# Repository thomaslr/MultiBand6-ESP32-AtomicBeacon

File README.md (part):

# MultiBand6-ESP32-AtomicBeacon: Hardware Atomic Clock Simulator

An open-hardware, low-power near-field radio transmitter built on the **ESP32-C3-Mini** with custom PCB designs, resonant magnetic antenna, 3D enclosure, and embedded web UI. Simulates authentic LF radio time signal broadcasts (**BPC, WWVB, MSF, DCF77, JJY40, JJY60**) to synchronize radio-controlled ("atomic") wristwatches and clocks over a localized range (~0.3 m to 1.0 m).

### 🏠 Real-World Setup & Confirmed Working
> **Built and actively in daily operation in Singapore!**  
> Since Singapore receives no LF signals from any of the official time towers, this device was built to solve that problem. It runs quietly every night on a bedroom nightstand, placed approximately **30 cm from a watch box**, successfully synchronizing a multi-watch collection every single night.
> 
> *(Compatible with all radio-controlled timepieces including **Casio G-Shock / Oceanus / Wave Ceptor / Lineage**, **Citizen Eco-Drive**, **Seiko**, **Timex**, **Junghans**, and standalone atomic desk clocks).*

| Assembled Hardware & Antenna | Bedroom Watch Box Deployment | 3 MultiBand 6 Watches Synced |
| :---: | :---: | :---: |
|  |  |  |
| *Custom 2-layer PCB with ESP32-C3 SuperMini & magnetic inductor antenna.* | *Operational placement ~30 cm from the watch box on the nightstand.* | *Simultaneous sync proof: Casio Wave Ceptor (`GET 1:02`), Lineage Chronograph, and Lineage Ana-Digi.* |

> [!IMPORTANT]
> **Wi-Fi & Network Time Requirement:**  
> The beacon does not contain a battery-backed hardware RTC chip. On boot and prior to each broadcast, it connects to your home 2.4 GHz Wi-Fi to fetch sub-second reference time from public NTP atomic clock servers (`pool.ntp.org`).  
> 
> **Placement Tip:** Place the beacon in a location with steady Wi-Fi reception (e.g. bedside or near your watch box where home Wi-Fi reaches). If placed in a Wi-Fi-dark dead zone on cold boot, the device cannot obtain the initial atomic epoch, and watch broadcasts/sync buttons will remain locked until time synchronization completes.

> [!TIP]
> 🚀 **Just want to get your watch syncing tonight?**  
> Check out the **[5-Minute Quick Start Guide](QUICKSTART.md)** for 1-click in-browser web flashing — zero software installation or coding required! For watch brand setup notes, see the **[Watch Compatibility Guide](CASIO_GUIDE.md)**.

---

## 1. Bill of Materials (BOM) & Components

| Component | Value / Specification | Role in Circuit | Rationale / Notes |
| :--- | :--- | :--- | :--- |
| **Microcontroller** | **ESP32-C3-Mini** | Core Controller & Carrier Generator | Single-core 32-bit RISC-V (160 MHz), hardware LEDC PWM with fractional clock divider, RTC timer, Wi-Fi 4, BLE 5. |
| **NPN Transistor** | **C1815 (2SC1815)** | Power Switch / RF Driver (Option A) | Small-signal NPN transistor (TO-92 package, E-C-B pinout) switching the LC tank at 5V for extended 1.0 m+ range. *(Note: You could also use a 2p2222 / 2N2222, but that transistor's different E-B-C pinout must be respected!)* |
| **Base Resistor ($R_{base}$)** | **$1\text{ k}\Omega$ (1/4 W)** | Transistor Base Drive (Option A) | Connects between GPIO 1 and C1815 Base (Pin 3). Limits base drive current to a safe $\sim 2.6\text{ mA}$ for saturation switching. |
| **Inductor ($L$)** | **16×18 3.5mH I-Type Inductor** | Magnetic Antenna ($H$-field radiator) | The reference hardware build specifically uses a **16×18 mm 3.5 mH I-type** (radial drum/bobbin core) power inductor. Its open magnetic circuit allows magnetic dipole flux lines to radiate into the room with low DC resistance. |
| **Tuning Capacitor ($C$)** | **1.5 nF (1500 pF / code `152`)** | Parallel LC Tank Resonator | Metallized Film (CBB / Polypropylene / Polyester) or C0G/NP0 ceramic. Rated $\ge 50\text{V}$. |
| **Damping Resistor ($R_{damp}$)** | **$220\,\Omega$ (1/4 W)** | Bandwidth Broadening & Safety Current Limiter | Lowers tank $Q$ to $\sim 6.5$, broadening bandwidth to $\sim 10\text{ kHz}$. Limits peak current to $\approx 23\text{ mA}$ in transistor booster or $\approx 15\text{ mA}$ in direct GPIO drive. |
| **DC Blocking Cap ($C_{block}$)** | **$1\,\mu\text{F}$ (or $100\text{ nF}$)** | DC Isolation & GPIO Protection (Option B) | Only required if running Option B (Direct GPIO Drive without transistor). Completely blocks DC current so pin cannot burn out if stuck `HIGH`. |

---

## 2. Hardware Circuit Schematics & Pinout

### Default Pin Assignment & ESP32-C3 SuperMini Pinout

The firmware defaults to **GPIO 1** for the antenna carrier output (`#define ANTENNA_PIN 1` in `src/main.cpp`).

| Board Pin | ESP32-C3 Signal | Role | Circuit Connection |
| :--- | :--- | :--- | :--- |
| **GPIO 1** | `IO1` (LEDC Ch 0) | **Default RF Carrier Out** | Connects to base resistor ($1\text{ k}\Omega$) driving booster NPN transistor, or direct antenna |
| **GPIO 2** | `IO2` | *(Unconnected)* | Strapping pin on ESP32-C3; reserved to prevent USB flashing and cold-boot issues |
| **GPIO 3** | `IO3` (Active LOW) | **Manual Sync Pushbutton** | Connects to tactile button `SW1` / external header `J3` with 10 kΩ pull-up |
| **GPIO 4** | `IO4` (I2C SDA) | **I2C Expansion (OLED)** | Connects to `J2` Pin 4 with 4.7 kΩ pull-up for 0.96" SSD1306 OLED display |
| **GPIO 5** | `IO5` (I2C SCL) | **I2C Expansion (OLED)** | Connects to `J2` Pin 3 with 4.7 kΩ pull-up for 0.96" SSD1306 OLED display |
| **GPIO 8** | `IO8` (Active LOW) | **Onboard Status LED** | Breathing nightstand pulse during active broadcast; 100% dark in standby |
| **5V / VIN** | `VBUS` (USB 5V) | Primary Power Rail | Supplies the booster circuit & damping resistor |
| **GND** | `GND` | Common Ground Return | Connects to transistor Emitter, capacitor ground, and ground plane |

> [!TIP]
> **Custom PCBs Available:**
> - **SMT Carrier Board (58×36 mm):** Located in [`pcb/smd/`](pcb/smd/) (or symlink [`smd/`](smd/)), uses 100% JLCPCB Basic Components ($0 setup fees) for fast turnkey assembly.
> - **Through-Hole DIY Edition (70×46 mm):** Located in [`pcb/hole-through/`](pcb/hole-through/) (or symlink [`hole-through/`](hole-through/)), 100% hand-solderable with standard through-hole passives, TO-92 transistor, DO-41 diode, and M3 mounting holes. Zero SMD parts required. See [`hole-through/README.md`](hole-through/README.md) for BOM and build guide.

> **Why GPIO 1?**
> * **Boot & Flashing Safety:** On the ESP32-C3, GPIO 2, 8, and 9 are hardware strapping pins. Pulling GPIO 2 low (which occurs when driving an NPN transistor base to ground) prevents entering Download Boot mode over USB and causes boot lockups. **GPIO 1 is a pure GPIO/ADC with zero strapping functions**, allowing reliable cold boots and in-circuit flashing over USB.
> * **LEDC Peripheral:** Native hardware routing to LEDC channel 0 with fractional divider clocking.
> * **Physical Placement:** Located on the accessible edge header directly adjacent to Pin 6 on the **ESP32-C3 SuperMini** (Pin 7).

```
      TOP VIEW (Component Side — looking at chip & buttons)
                       ┌───[ USB-C ]───┐
     [BOOT Button Side]│               │[RST Button Side]
              GPIO 5   │ [ ]       [ ] │   5V          <── Top-Right (next to USB)
              GPIO 6   │ [ ]       [ ] │   GND (G)     <── Next to 5V
              GPIO 7   │ [ ]       [ ] │   3V3 (3.3)   <── Regulated 3.3V
              GPIO 8   │ [ ]       [ ] │   GPIO 4
              GPIO 9   │ [ ]       [ ] │   GPIO 3
             GPIO 10   │ [ ]       [ ] │   GPIO 2
             GPIO 20   │ [ ]       [■] │   GPIO 1      <── [■] ANTENNA OUT (Pin 7)
   (Pin 21)  GPIO 21   │ [ ]       [ ] │   GPIO 0      (Pin 0)
                       └──[ Antenna ]──┘

      BOTTOM VIEW (Underside — looking at PCB silkscreen labels)
                       ┌───[ USB-C ]───┐
                       │               │
     Top-Left (5V) ──► │ [ ]       [ ] │   GPIO 5
              GND (G)  │ [ ]       [ ] │   GPIO 6
            3V3 (3.3)  │ [ ]       [ ] │   GPIO 7
               GPIO 4  │ [ ]       [ ] │   GPIO 8
               GPIO 3  │ [ ]       [ ] │   GPIO 9
               GPIO 2  │ [ ]       [ ] │   GPIO 10
   ANTENNA OUT ──────► │ [■]       [ ] │   GPIO 20
     (Pin 0)   GPIO 0  │ [ ]       [ ] │   GPIO 21     (Pin 21)
                       └───────────────┘
```

---

### Option A: C1815 NPN Transistor Booster Circuit (Recommended for 1.0 m+ Range)

This configuration uses the **C1815 (2SC1815) NPN** transistor powered directly from the **5V USB rail**. It isolates the ESP32 silicon and delivers $3\times$ to $5\times$ more magnetic flux for extended range:

```
                                  +5V (from ESP32 5V / VIN Pin)
                                    │
                                    ├───[ 220 ohm ]─── (R_damp)
                                    │
                                    ├───┬───────────────┬───┐
                                     │   │               │   │
                                     │  [16x18 3.5mH] [ 1.5 nF ]  (Parallel LC Tank)
                                     │  (I-type Ind.) (Capacitor)
                                     │   │               │   │
                                     └───┴───────────────┴───┘
                                                 │
                                                 ▼
                                          [ C ] Collector (Pin 2)
   ESP32-C3 GPIO 1 ──[ 1k ohm ]────────── [ B ] Base (Pin 3)       C1815 NPN Transistor
   (Default PWM Out) (R_base)             [ E ] Emitter (Pin 1)
                                                 │
                                                 ▼
   ESP32-C3 GND ─────────────────────────────────┴─── Common Ground (GND)
```

#### Why This Works Well:
1. **Zero Stress on ESP32:** The GPIO 1 pin only sources a safe $I_B \approx 2.6\text{ mA}$ into the base through the $1\text{ k}\Omega$ base resistor ($V_{GPIO} = 3.3\text{V}$, $V_{BE} \approx 0.7\text{V}$).
2. **5V Swing:** The LC tank swings around the 5V rail rather than 3.3V, pushing significantly more magnetic current through the 3.5 mH inductor.
3. **Uses Your $220\,\Omega$ Resistor:** The $220\,\Omega$ damping resistor limits peak collector current to a cool, safe $\approx 23\text{ mA}$ while maintaining the broad $\sim 10.7\text{ kHz}$ bandwidth so 68.5 kHz BPC resonates smoothly.
4. **Broadcast Range:** Up to **1.0 m – 1.2 m**.

#### C1815 Transistor Pinout & Pinout Connections (TO-92 Package)

The circuit is designed specifically around the **C1815 (2SC1815)** small-signal NPN transistor.

Looking at the **flat printed face** (labeled "C1815") with the leads pointing downwards, the pinout follows the standard Asian / JIS **E-C-B** configuration:

```
          TO-92 Package (Front View)
               ┌───────────┐
               │   C1815   │   <── Flat Printed Face
               │   GR 331  │
               └─┬───┬───┬─┘
                 │   │   │
                 1   2   3
                 E   C   B
```

| Pin # | Lead Name | Circuit Function | Breadboard Connection |
| :---: | :--- | :--- | :--- |
| **Pin 1 (Left)** | **Emitter (E)** | Common Ground Return | Connects directly to **(-) Blue GND Rail** (Row 13) |
| **Pin 2 (Center)** | **Collector (C)** | Switched LC Tank Low Side | Connects to **Row 12** (bottom of 3.5 mH inductor & 1.5 nF cap) |
| **Pin 3 (Right)** | **Base (B)** | RF Carrier PWM Input | Connects to **Row 11** (receives drive from GPIO 1 via $1\text{ k}\Omega$ resistor) |

> [!NOTE]
> **Orientation Tip:** Because **Base is Pin 3 (Right)** on the C1815, mounting the transistor with its flat face facing right puts Pin 3 (Base) at **Row 11**, directly adjacent to ESP32 GPIO 1 (Row 7). This allows the $1\text{ k}\Omega$ base resistor to bridge Rows 7 and 11 neatly without any crossing wires.

> [!WARNING]
> **Can you use a 2p2222 (2N2222 / PN2222) instead?**
>
> You **can** use a **2p2222** (commonly labeled **2N2222** or **PN2222**) NPN transistor if a C1815 is unavailable, **BUT that transistor's completely different pinout must be respected!**
>
> * **C1815 (Asian / JIS):** `Pin 1 = Emitter (E) | Pin 2 = Collector (C) | Pin 3 = Base (B)` — **E - C - B**
> * **2p2222 / 2N2222 (American / JEDEC TO-92):** `Pin 1 = Emitter (E) | Pin 2 = Base (B) | Pin 3 = Collector (C)` — **E - B - C**
>
> **Crucial wiring differences to respect when using 2p2222:**
> 1. **Base pin location is swapped:** On a 2p2222, **Base is the middle pin (Pin 2)** instead of Pin 3. The $1\text{ k}\Omega$ base resistor from GPIO 1 must be routed to **Pin 2 (Center)**.
> 2. **Collector pin location is swapped:** On a 2p2222, **Collector is the right pin (Pin 3)** instead of Pin 2. The LC tank low side must be routed to **Pin 3 (Right)**.
> 3. **Emitter:** Pin 1 (Left) remains Emitter (GND) on both transistors.
>
> If you drop a 2p2222 / 2N2222 directly into the breadboard using the C1815 layout without adjusting the pin wiring, the Base and Collector will be reversed, the transistor will not switch, and the beacon will fail to broadcast.

| Transistor Model | Pinout Standard | Pin 1 (Left) | Pin 2 (Center) | Pin 3 (Right) | Required Wiring in this Circuit |
| :--- | :---: | :---: | :---: | :---: | :--- |
| **C1815 (Default)** | **JIS (E-C-B)** | **Emitter (E)** | **Collector (C)** | **Base (B)** | Pin 1 $\rightarrow$ GND, Pin 2 $\rightarrow$ LC Tank (Row 12), Pin 3 $\rightarrow$ $1\text{ k}\Omega$ to GPIO 1 (Row 11) |
| **2p2222 / 2N2222 (Alternative)** | **JEDEC (E-B-C)** | **Emitter (E)** | **Base (B)** | **Collector (C)** | Pin 1 $\rightarrow$ GND, Pin 2 $\rightarrow$ $1\text{ k}\Omega$ to GPIO 1, Pin 3 $\rightarrow$ LC Tank *(Pinout must be respected!)* |

---

### Option B: Direct GPIO Drive (Minimalist Bench / Desk Use)

This configuration connects directly to ESP32-C3 GPIO 1 with built-in safety against DC overcurrent and back-EMF spikes:

```
                           C_block       R_damp
                          [ 1 uF ]     [ 220 ohm ]
  ESP32-C3 GPIO 1 ---------[ || ]--------[ \/\/\ ]---------+-----------------+
  (Default PWM Out)                                        |                 |
                                                        +------+          +------+
                                                        |      |          |      |
                                                     16x18 3.5mH  Inductor 1.5 nF Cap
                                                     (I-Type)             (CBB/Ceramic)
                                                        |      |          |      |
                                                        +------+          +------+
                                                           |                 |
  ESP32-C3 GND --------------------------------------------+-----------------+
```

#### Circuit Analysis & Parameters
* **Nominal Resonance:**
  $$f_0 = \frac{1}{2\pi \sqrt{L \cdot C}} = \frac{1}{2\pi \sqrt{3.5\times 10^{-3} \cdot 1.5\times 10^{-9}}} \approx 69.46\text{ kHz}$$
* **Characteristic Impedance ($Z_0$):**
  $$Z_0 = \sqrt{\frac{L}{C}} = \sqrt{\frac{3.5\times 10^{-3}}{1.5\times 10^{-9}}} \approx 1527\,\Omega$$
* **Effective Quality Factor ($Q$ with $R_{damp} = 220\,\Omega$):**
  $$Q \approx \frac{Z_0}{R_{total}} = \frac{1527\,\Omega}{220\,\Omega + R_{coil}} \approx \mathbf{6.5}$$
* **Passband Bandwidth ($\Delta f$):**
  $$\Delta f = \frac{f_0}{Q} \approx \frac{69.5\text{ kHz}}{6.5} \approx \mathbf{10.7\text{ kHz}}\quad (64\text{ kHz} \text{ to } 75\text{ kHz})$$
  * Because the passband is over $10\text{ kHz}$ wide, **BPC at 68.5 kHz sits comfortably near peak resonance**, fully absorbing the $\pm 10\%$ manufacturing tolerances of the coil and capacitor without requiring precision trimming.
* **Pin Current:**
  $$I_{peak} \approx \frac{3.3\text{ V}}{220\,\Omega} \approx \mathbf{15\text{ mA}} \quad (\text{Safe: below ESP32-C3 20 mA maximum})$$

---

### Breadboard Wiring Layout (C1815 NPN Booster Circuit)

> 🎨 **Visual Diagram:** A full vector graphic illustration is available in [breadboard_layout.svg](pcb/breadboard/breadboard_layout.svg) or viewable in your browser via [breadboard_layout.html](pcb/breadboard/breadboard_layout.html). (See also [`pcb/breadboard/`](pcb/breadboard/)).

Here is the top-down terminal row mapping for a standard breadboard with the **ESP32-C3 SuperMini mounted directly across the center ravine**:

```
  (+) POWER RAIL  [+5V from ESP32 Pin F1]  ─── (Red Line)
  (-) GROUND RAIL [GND from ESP32 Pin F2]  ─── (Blue Line)

   Row    [A B C D E]  (Center Ravine)  [F G H I J]
  ────────────────────────────────────────────────────────────────────────
   01:    [ . . . . . ] ── [ESP32-C3] ── [ 5V ]  [ . . . . ] ── Wire to (+) 5V Rail
   02:    [ . . . . . ] ── [SuperMini]── [ GND ] [ . . . . ] ── Wire to (-) GND Rail
   03:    [ . . . . . ] ── [ Rows   ] ── [ 3V3 ] [ . . . . ]
   04:    [ . . . . . ] ── [ 1 to 8 ] ── [ IO4 ] [ . . . . ]
   05:    [ . . . . . ] ── [ across ] ── [ IO3 ] [ . . . . ]
   06:    [ . . . . . ] ── [ ravine ] ── [ IO2 ] [ . . . . ]
   07:    [ . . . . . ] ── [        ] ── [ IO1 ] [ . . . . ] ── [ 1k R_base ]
   08:    [ . . . . . ] ── [        ] ── [ IO0 ] [ . . . . ]          │
                                                                      │
   11:    [ . . . . . ]                  [ . . . . . ] ── C1815 BASE (B, Pin 3) ◄─┘ (Closest to IO1!)
   12:    [ . . . . . ]                  [ . . . . . ] ── C1815 COLLECTOR (C, Pin 2)
                                               │
                                       ┌───────┴───────────────┐
                                       │ 16x18 3.5mH I-Type Ind│  (Parallel LC Tank: Rows 12–16)
                                       │ 1.5nF Capacitor       │  (Col F: Cap, Col H: Inductor)
                                       └───────┬───────────────┘
                                               │
   13:    [ . . . . . ]                  [ . . . . . ] ── C1815 EMITTER (E, Pin 1) ── Wire to (-) Blue GND
   ...
   16:    [ . . . . . ]                  [ . . . . . ] ── LC Tank High Side
                                               │
                                         [ 220 ohm ]   ── R_damp connects directly
                                               │          from Row 16 to (+) 5V Rail
  ────────────────────────────────────────────────────────────────────────
```

#### Step-by-Step Breadboard Connections:
1. **Mount the ESP32-C3 SuperMini:**
   * Plug the module directly into **Rows 1 to 8** spanning the center ravine:
     * **Column E (Left):** GPIO 5 down to GPIO 21 (all left pins open).
     * **Column F (Right):** Pin **F1 = 5V**, **F2 = GND**, Pin **F7 = GPIO 1 (Antenna Out)**.
2. **Power Rails:**
   * Add a short red jumper wire from **Row 1 (Col G)** to the **(+) Red Rail**.
   * Add a short black jumper wire from **Row 2 (Col G)** to the **(-) Blue Rail**.
3. **C1815 NPN Transistor (JIS E-C-B Pinout):**
   * Plug into **Rows 11, 12, and 13** in Column G with the **flat printed face facing right** (curved dome to the left):
     * **Row 11 = Base (B, Pin 3)** $\rightarrow$ Closest to GPIO 1; receives base drive from the $1\text{ k}\Omega$ resistor.
     * **Row 12 = Collector (C, Pin 2)** $\rightarrow$ Switched output; connects to the parallel LC tank low side.
     * **Row 13 = Emitter (E, Pin 1)** $\rightarrow$ Add a short black jumper from Row 13 (Col I) to the **(-) Blue GND Rail**.
   > [!NOTE]
   > **Note on substituting a 2p2222 (2N2222 / PN2222):** You could use a 2p2222 / 2N2222 instead, but you must respect that transistor's different **E-B-C** pinout: its center pin (Pin 2) is Base and its right pin (Pin 3) is Collector. If substituted, the $1\text{ k}\Omega$ resistor from GPIO 1 must go to the center pin (Base), and the LC tank must connect to the right pin (Collector).
4. **Base Drive Resistor ($1\text{ k}\Omega$):**
   * Plug one leg of the **$1\text{ k}\Omega$ resistor** into **Row 7 (Col I)** (directly taps ESP32 GPIO 1).
   * Plug the other leg into **Row 11 (Col I)** (directly taps the C1815 Base, Pin 3). Clean direct bridge without crossing wires!
5. **LC Tank (Parallel Inductor + Capacitor):**
   * Plug the **1.5 nF Capacitor** across **Row 12 (Col F)** and **Row 16 (Col F)** (inner position, towards center ravine for clearance).
   * Plug the **16×18 3.5mH I-type Inductor** across **Row 12 (Col H)** and **Row 16 (Col H)** (outer position, nearer breadboard edge for maximum RF radiation & easy watch placement).
6. **Damping Resistor ($220\,\Omega$):**
   * Plug one leg of the **$220\,\Omega$ resistor** into **Row 16 (Col J)**.
   * Plug the other leg directly into the **(+) Red 5V Rail**.
---

### Custom PCB Carrier Board (JLCPCB SMT-Ready)

For a permanent, enclosure-friendly installation, a production-grade 2-layer carrier PCB is provided in the [`pcb/`](pcb/) folder:

| 3D Perspective | Top Layout View |
|:---:|:---:|
|  |  |

* **Form Factor:** Clean **58 mm × 36 mm** with 4× M2.5 corner mounting holes.
* **100% Free JLCPCB SMT Setup ($0.00 Part Loading Fee):** Pre-assembled with only 7 SMD components (MMBT2222A NPN switch, flyback clamp diode, 0805 resistors/capacitors) — all verified **JLCPCB Basic Components**.
* **Zero Bedside Light Pollution:** No LEDs on the carrier PCB to keep the bedroom dark at night. The ESP32-C3 SuperMini's onboard blue LED (GPIO 8) handles the soft breathing rhythm during active broadcasts while remaining completely dark in standby.
* **Dual Antenna & Tuning Flexibility:**
  * Solder the **16×18 mm 3.5 mH I-type inductor** directly into the labeled onboard footprint (`L1`).
  * Connect an external ferrite rod or loop antenna via the dedicated **2-pin screw terminal block** (`J1`, KF301-2P, 5.08 mm pitch), located well clear of `L1` for easy screwdriver and wire access.
  * Fine-tune or customize tank resonance via the **through-hole capacitor socket** (`C2`, standard 5.08 mm pitch for film/ceramic caps).
* **Instant Ordering:** Pre-generated Gerber archive (`MultiBand6_Beacon_Gerbers.zip`), BOM (`bom.csv`), and centroid placement (`positions.csv`) files are ready to drag-and-drop into [JLCPCB](https://jlcpcb.com/).
* See the [**PCB Ordering & Assembly Guide**](pcb/README.md) for full instructions.

### 3D Printable Multi-Mount Enclosure & Table Stand

For a clean, safe bedside installation, full 3D printable models are provided in the [`enclosure/`](enclosure/) folder:
* **Vertical Surface Mounting:** Features dual M3 screw mounting ears, cross-recessed cable-tie channels (for bedframes/poles), and a 3M Command / VHB tape well.
* **Horizontal Nightstand / Desk Stand:** An attachable snap-on cradle with a **$45^\circ$ tilt angle** aiming the magnetic coil upward toward your watch, complete with anti-slip rubber foot recesses.
* **No Supports Required:** All STLs print cleanly flat on standard beds. See [`enclosure/README.md`](enclosure/README.md) for STL downloads and OpenSCAD sources.

---

## 3. Quick Start: First-Time Setup & Flashing (ESP32-C3 SuperMini)

> [!TIP]
> Prefer a streamlined, step-by-step guide? Follow the dedicated **[5-Minute Quick Start Guide](QUICKSTART.md)**.

For new users setting up an **ESP32-C3 SuperMini** for the first time, you do **not** need to install Rust or compile code. Everything is pre-built and packaged for instant browser or USB flashing.

### 📦 Where to Get the Firmware Binaries

Every GitHub release provides two distinct binaries on the **[Releases Page](https://github.com/thomaslr/MultiBand6-ESP32-AtomicBeacon/releases)**:

| Binary File | Flash Address | Purpose & Usage |
| :--- | :---: | :--- |
| **`multiband6-beacon-factory.bin`** *(~1.6 MB)* | **`0x0`** | **Initial Setup / First-Time Flashing:** Merged factory binary containing the ESP32-C3 bootloader, Dual-OTA partition table (`ota_0` and `ota_1`, 1984 KB each), and application code. Flashes blank chips in one shot. |
| **`multiband6-beacon.bin`** *(~1.5 MB)* | OTA Partition | **Wi-Fi Updates (OTA):** Standalone application payload uploaded via the web interface (`http://timestation.local`) or downloaded during remote updates. |

---

### ⚠️ Pre-Flashing Hardware Checklist

1. **Certified USB-C Data Cable:** Many USB-C cables are charge-only. The ESP32-C3 SuperMini uses its internal native USB-Serial/JTAG controller, which requires data lines ($D+$ and $D-$).
2. **Antenna Pin Warning (GPIO 1 vs GPIO 2):**
   * Keep the transmitter circuit connected to **GPIO 1** (`IO1`).
   * **Do NOT ground or connect GPIO 2 during flashing:** GPIO 2 is an ESP32-C3 strapping pin. Pulling it LOW (e.g. through a transistor base resistor) blocks the ROM bootloader and prevents entering USB download mode.
3. **Putting ESP32-C3 SuperMini into Download Boot Mode:**
   If the flasher does not auto-detect the board:
   * Press and hold the **`BOOT`** button (GPIO 9).
   * Press and release the **`RST`** button (or plug in the USB cable while holding `BOOT`).
   * Release the **`BOOT`** button. The chip is now in download mode.

---

### 🚀 Flashing the Board

#### Option 1: 1-Click Online Web Installer (Easiest — Zero File Downloads)

Compatible with **Google Chrome** and **Microsoft Edge**:

1. Connect your ESP32-C3 SuperMini via USB (data cable).
2. Put the board into download mode: Hold **`BOOT`** $\rightarrow$ tap **`RST`** $\rightarrow$ release **`BOOT`**.
3. Open the **[TimeStation 1-Click Web Installer](https://thomaslr.github.io/MultiBand6-ESP32-AtomicBeacon/)**.
4. Click **"⚡ Install TimeStation Beacon"**, select your serial port, and wait for flashing to reach 100%.
5. The installer will even prompt you to configure your Wi-Fi directly in the browser!

---

#### Option 2: In-Browser Web Flasher (Espressif esptool-js)

1. Connect your ESP32-C3 SuperMini via USB.
2. Put the board into download mode (Hold `BOOT` $\rightarrow$ tap `RST` $\rightarrow$ release `BOOT`).
3. Open the **[Espressif Web Flasher (esptool-js)](https://espressif.github.io/esptool-js/)** or **[Adafruit WebSerial ESPTool](https://adafruit.github.io/Adafruit_WebSerial_ESPTool/)**.
4. Set Baud Rate to **`460800`** and click **Connect**. Choose your ESP32-C3 port.
5. In the file upload section:
   * **File:** Select `multiband6-beacon-factory.bin` downloaded from [Releases](https://github.com/thomaslr/MultiBand6-ESP32-AtomicBeacon/releases).
   * **Flash Address:** **`0x0`** (or `0x0000`).
6. Click **Program / Flash**.
7. Once finished, press the **`RST`** button once to boot the beacon!

---

#### Option 3: Single-Command USB CLI (`esptool.py` or `espflash`)

If you have Python or `espflash` installed, flash the merged factory image directly to address `0x0`:

```bash
# Using esptool.py (Python)
esptool.py --chip esp32c3 write_flash 0x0 multiband6-beacon-factory.bin

# Or using espflash (Rust CLI)
espflash write-bin 0x0 multiband6-beacon-factory.bin
```

Press **`RST`** once when complete.

---

#### Option 4: Compiling & Flashing from Source (Rust Nightly)

For developers working directly on the codebase:

```bash
cd firmware-rust/beacon-firmware
cargo run --release
```
*(The repository's `.cargo/config.toml` automatically invokes `espflash flash --partition-table beacon-firmware/partitions.csv --monitor`, provisioning the Dual-OTA partition table, building the bootloader, flashing the app, and launching the serial monitor).*

---

### 📶 First-Time Wi-Fi Provisioning (SoftAP & Captive Portal)

On first boot, the ESP32-C3 has no saved Wi-Fi credentials in NVS, so it automatically launches its configuration hotspot:

1. **Connect to Hotspot:** On your smartphone or laptop, connect to the open Wi-Fi network:
   $$\mathbf{TimeStation\text{-}Setup\text{-}XXXX}$$
   *(where `XXXX` is the last 4 hex characters of your ESP32's MAC address).*
2. **Open Setup Portal:** The captive portal will open automatically. If not, open your browser and navigate to:
   **[http://192.168.4.1](http://192.168.4.1)**
3. **Configure Wi-Fi & Station:**
   * Scan and pick your home 2.4 GHz Wi-Fi network, enter the password.
   * Choose your default atomic radio station (e.g. **WWVB**, **DCF77**, **MSF**, **BPC**, **JJY**) or select **Carousel Mode**.
   * Click **Save & Connect**.
4. **Access Web Dashboard:** The device will reboot and join your local network. Open:
   **[http://timestation.local](http://timestation.local)** *(or check your router DHCP table for its IP address)*.

---

## 4. Physical Antenna Alignment & Orientation

* The **16×18 3.5mH I-type inductor** (16 mm diameter × 18 mm height drum core) radiates a magnetic dipole field oriented along its **vertical cylindrical axis** (top and bottom flat faces).
* Most atomic clocks and watches (such as Casio MultiBand 6, Citizen Eco-Drive, Seiko, or Timex) contain a **horizontal ferrite rod antenna** embedded inside the case (commonly at 12 o'clock or 9 o'clock).
* **Optimal Placement:** Position the inductor so that the magnetic flux lines looping out of the inductor's ends pass directly through the clock's internal antenna bar (parallel orientation).
* **Broadcast Range:** 
  * **C1815 NPN Booster (Option A):** Approx. **1.0 m to 1.2 m** (extended coverage for watches across a room or dresser).
  * **Direct GPIO with $220\,\Omega$ (Option B):** Approx. **0.5 m to 0.7 m** (ideal for close proximity bedside table or desk).

---

## 5. Supported Stations & Broadcast Signals

| Station | Location | Frequency | Modulation Protocol | Frame Duration |
| :--- | :--- | :---: | :--- | :---: |
| **BPC** | China (Shangqiu) | **68.5 kHz** | 4-state pulse width keying (100–400 ms) | 20 seconds |
| **WWVB** | USA (Colorado) | **60.0 kHz** | AM pulse width keying (0.2s = 0, 0.5s = 1, 0.8s = marker) | 60 seconds |
| **MSF** | UK (Anthorn) | **60.0 kHz** | OOK (Carrier 100% off for 100/200/300/500 ms) | 60 seconds |
| **DCF77** | Germany (Mainflingen) | **77.5 kHz** | AM carrier reduction to 15% (100 ms = 0, 200 ms = 1) | 60 seconds |
| **JJY40** | Japan East (Fukushima) | **40.0 kHz** | AM pulse width keying | 60 seconds |
| **JJY60** | Japan West (Kyushu) | **60.0 kHz** | AM pulse width keying | 60 seconds |
| **Custom** | Global | User Selectable | User-defined UTC offset & simulated station format | — |

---

## 6. Software Stack & 100% Rust Architecture

This project is written in **100% pure Rust** targeting `riscv32imc-esp-espidf` using the official Espressif `esp-idf-svc` and `embedded-svc` framework. All legacy C++ and PlatformIO code has been eliminated.

### Architecture Overview
* **`firmware-rust/beacon-core`**: A hardware-independent library containing the atomic time signal protocols (`BPC`, `WWVB`, `MSF`, `DCF77`, `JJY40`, `JJY60`), astronomical calendar math, and configuration schemas. Can be tested natively on macOS/Linux with standard `cargo test`.
* **`firmware-rust/beacon-firmware`**: The embedded binary running on the ESP32-C3:
  * **LEDC Hardware Carrier**: Modulates the RF magnetic carrier on **GPIO 1** with fractional divider precision at 80 MHz.
  * **High-Resolution 50ms Timer**: Drives the bitstream tick pulses with microsecond precision.
  * **Status LED Nightstand Breathing Wave**: Smooth 4.0-second sine wave on GPIO 8 during active transmission; 100% dark in standby.
  * **Bedside Manual Sync Button**: Tactile button on GPIO 3 (Active LOW) with software debounce.
  * **Embedded Web UI**: Pre-compresses assets with Gzip at build time, serving both raw and `.gz` payloads.

---

## 7. Flash Partitioning & Mandatory Dual-OTA Updates

> [!IMPORTANT]
> **Dual-OTA Partitioning is strictly mandatory.** The partition table must NEVER revert to a single-partition or factory-only layout.

The ESP32-C3 4MB SPI Flash is partitioned into two identical application slots (`ota_0` and `ota_1`), enabling seamless remote updates with automatic crash rollback:

```csv
# ESP-IDF Partition Table for 4MB Flash Dual-OTA (1984KB per slot)
# Name,   Type, SubType, Offset,   Size,     Flags
nvs,      data, nvs,     0x9000,   0x6000,
otadata,  data, ota,     0xf000,   0x2000,
phy_init, data, phy,     0x11000,  0x1000,
ota_0,    app,  ota_0,   0x20000,  0x1f0000,
ota_1,    app,  ota_1,   0x210000, 0x1f0000,
```

* **Capacity**: Each application slot provides **1,984 KB** (2,031,616 bytes) of flash space.
* **Bootloader Rollback**: `CONFIG_BOOTLOADER_APP_ROLLBACK_ENABLE=y` ensures that if a newly flashed binary panics or crashes on boot, the bootloader automatically reverts to the previous working slot.
* **Update Methods**:
  * **Remote HTTPS Streaming**: Direct download from GitHub Releases via `/api/ota/update`.
  * **Direct Browser Upload**: Drag-and-drop or file upload of local `multiband6-beacon.bin` via `/api/ota/upload`.

---

## 8. Wi-Fi Resilience, Power & SoftAP Provisioning

Learned from the `plant-esp32` architecture:

### 1. WPA3-SAE Stale Session Recovery
Modern routers and mesh nodes (e.g. TP-Link Deco, ASUS AiMesh) frequently reject immediate reconnections after a restart (`reason: 0x600`). The firmware implements a 10-attempt retry loop with complete radio cycling before falling back.

### 2. First-Time SoftAP Provisioning & Captive Portal
* If no credentials exist in NVS (or connection attempts fail), the device automatically starts SoftAP `TimeStation-Setup-XXXX` (using the last 4 characters of the MAC) at **192.168.4.1**.
* Mobile devices opening the hotspot are automatically greeted by the captive portal (`setup.html`).
* Users can scan nearby 2.4 GHz networks (`/api/scan`), pick their SSID, enter their password, and reboot the device directly into station mode.
* **5-Minute Self-Healing Recovery Timer**: If credentials exist in NVS but the router was temporarily power-cycled, the beacon automatically reboots every 5 minutes in setup mode to reconnect once the router recovers.

### 3. RF Noise Suppression & Power Hygiene
* **Standby Mode**: 802.11 Modem-Sleep (`WIFI_PS_MIN_MODEM`) and 80 MHz CPU clock minimize power consumption (~15–20 mA average).
* **Broadcast Mode**: Modem-sleep is paused during active LF carrier transmission to eliminate 3.3V rail ripple and 2.4 GHz RF burst hash that could interfere with wristwatch antenna correlation.
* **Bandwidth & Power**: Station radio locked to 20 MHz (HT20) with configurable TX power up to 78 (~19.5 dBm max).
* **mDNS Responder**: Device is accessible at `http://timestation.local`.

---

## 9. Web Dashboard & Operational Features

The ESP32-C3 hosts an embedded single-page responsive web dashboard (`http://timestation.local`):

### 1. Broadcast Control Tab
* **Single Station Mode:** Continuous broadcast on BPC, WWVB, MSF, DCF77, JJY40, or JJY60.
* **Carousel Mode ("World Tour"):** Rotates through selected stations (e.g. BPC $\rightarrow$ WWVB $\rightarrow$ JJY60):
  * Configurable duration per station (e.g. 15 minutes per station $\times$ 3 stations = 45-minute nightly window).
  * **Clean Minute Boundary Handoff:** The ESP32-C3 hardware LEDC timer retunes carrier frequency dynamically on the fly at the exact `:00` second mark, ensuring no watch receiver encounters truncated minute frames.
  * Live dashboard displays active carousel stage and real-time countdown timers.
* **Live Clocks:** Displays live synchronized UTC atomic time and local station time.
* **Daily Schedule:** Configurable start time (e.g. `02:00 AM`) and duration.

### 2. Network & Wi-Fi Settings Tab
* **Active Status:** Live SSID, IP address, Gateway, RSSI signal meter, MAC address, and mDNS name.
* **Nearby Wi-Fi Scanner:** Discovers nearby 2.4 GHz access points with signal strength.
* **Credentials Management:** Save new Wi-Fi credentials with show/hide password toggle.
* **NTP Server Configuration:** Select or customize atomic time server (`pool.ntp.org`, `time.google.com`, `time.cloudflare.com`).
* **Radio Tuning:** Toggle modem-sleep, select max TX power (78 / 68 / 60 / 44), and toggle HT20 mode.
* **Maintenance:** One-click "Reset Wi-Fi (Setup Mode)" and "Reboot ESP32" buttons.

### 3. Firmware & Dual-OTA Tab
* Real-time partition status (running slot, target slot, package version, rollback safety).
* Remote update trigger from URL (GitHub Releases).
* Direct browser file upload of `multiband6-beacon.bin` with live progress bar.

### 4. Diagnostics & Live Log Console Tab
* **Live System Log Terminal:** Monospaced real-time scrolling console showing NTP synchronizations, carrier phase tuning, and Wi-Fi health without requiring a USB serial cable.
* **Hardware Telemetry:** Live free heap memory, minimum free heap watermark, Wi-Fi RSSI signal meter, and system uptime.
* **Console Controls:** Auto-scroll toggle, one-click clipboard copy, and buffer clear.

### 5. Interactive Info Popovers (`ℹ️`)
Every setting and hardware parameter includes an interactive `ℹ` info icon powered by a responsive, touch-friendly popover engine:
* **Desktop:** Smooth hover activation (`mouseenter` / `mouseleave`).
* **Mobile & Touchscreens:** Tap to open and pin the card; tap outside, tap the `×` button, or press `Esc` to dismiss.
* **Viewport Clamping:** Popovers dynamically calculate positions relative to the screen to prevent edge clipping on mobile displays.
* **Contextual Help Provided:**
  * **Time Signal Stations:** Frequencies, regions, and matching Casio city codes (`BPC` $\rightarrow$ HKG/BJS, `WWVB` $\rightarrow$ NYC/LAX, `MSF` $\rightarrow$ LON, `DCF77` $\rightarrow$ BER/PAR/ROM/ATH, `JJY` $\rightarrow$ TYO).
  * **Broadcast Duration:** Explains why 20–25 minutes is optimal for Casio correlation.
  * **Overnight Calibration:** Explains why Casio watches default to searching at 2:00 AM.
  * **Antenna Pin (GPIO 1):** Explains the LEDC PWM carrier, C1815 driver, and tuned LC tank.
  * **NTP Time Server:** Explains Stratum-1/Stratum-2 atomic clock routing.

### 6. Timezone Offset: Mechanics & World Time Limits

The web interface provides a manual **Custom Time Offset** ($\pm 12$ hours) with a dynamic warning banner:

#### Intended Use Cases
* **Standalone Atomic Wall & Desk Clocks:** Many digital atomic clocks (Braun, Oregon Scientific, AcuRite, Citizen desktop stations) have no timezone configuration setting and simply display whatever time is received on their fixed carrier frequency. For these devices, the offset allows displaying local time.
* **Single-Timezone Wristwatch Wearers:** Users who wear their watch solely for local time on the main display and do not use secondary timezone modes.

#### ⚠️ Critical Limitation: Effects on Multi-Timezone & World Time Clocks
Casio MultiBand 6 watches (G-Shock, ProTrek, Lineage, Oceanus) calculate their internal time using a **single internal UTC baseline**:

$$\text{Internal UTC} = \text{Received Radio Time} - \text{Home City UTC Offset}$$

When the watch enters **World Time (WT)** mode, it dynamically calculates:

$$\text{World Time Display} = \text{Internal UTC} + \text{WT City Offset}$$

**What happens when you apply a transmitter offset:**
1. If your watch's Home City is set to `HKG` (Hong Kong, UTC+8) and you apply an ESP32 offset of **-5 hours** to spoof Jeddah local time (UTC+3):
   * The watch receives 15:00 and calculates: $\text{Internal UTC} = 15\text{:}00 - 8\text{h} = \mathbf{07\text{:}00\text{ UTC}}$ (which is 5 hours behind real-world UTC).
   * Your main watch display shows **15:00** (Jeddah time).
   * **The Consequence:** Because the watch's internal UTC anchor is skewed by $-5\text{ hours}$, **every single city in World Time mode (e.g. LON, NYC, TYO) will also be shifted backwards by 5 hours and display incorrect times**.

#### Recommended MultiBand 6 Best Practice
If you use World Time mode on your watch:
1. Keep the beacon offset set to **0** (Native transmitter time).
2. Set your watch's **Home City** to a supported radio transmitter city (e.g. `HKG` for BPC, or `BER`/`ATH` for DCF77).
3. Set your watch's **World Time** to your actual local destination city (e.g. `JED`).
4. Use the watch's built-in **Home/World Time quick-swap shortcut** (e.g. pressing `[Adjust] + [Light]` simultaneously on module 3159 / 3495). Both timezones remain mathematically accurate.

#### Live Dynamic Web Notice
* **Offset = 0:** Displays a green neutral banner: `✓ Native Time (0h Offset): Broadcasts authentic station time. Recommended for MultiBand 6 watches to maintain accurate World Time.`
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
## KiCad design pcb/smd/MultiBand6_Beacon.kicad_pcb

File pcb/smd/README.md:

# MultiBand 6 ESP32-C3 Atomic Beacon — SMT Carrier Board (58×36 mm)

A compact, professional 2-layer carrier PCB designed in KiCad for the **MultiBand 6 ESP32 Atomic Clock Beacon**.

This board integrates the high-efficiency RF switching driver, flyback clamp, resonant LC tank, power filtering, and dual antenna connections (onboard 16×18 mm 3.5 mH inductor + external antenna screw terminal block) into a clean **58 mm × 36 mm** footprint with corner M2.5 mounting holes.

All surface-mount components (SMD) have been specifically selected from **[JLCPCB's Basic Component Library](https://jlcpcb.com/)**, meaning they are pre-loaded in JLCPCB's automated pick-and-place feeders and incur **$0.00 setup / reel loading fees** for turnkey SMT assembly.

---

## 3D Renders

| Isometric Perspective | Top Layer Layout |
|:---:|:---:|
|  |  |

---

## Key Hardware Features

1. **Boot-Safe RF Output (`GPIO 1`):**
   * Driven from **GPIO 1** (Pin 15 on ESP32-C3 SuperMini).
   * **100% Strapping Safe:** Unlike GPIO 2 (which is an ESP32-C3 strapping pin that prevents download/flashing if pulled low), GPIO 1 has zero bootloader functions. This allows firmware updates over USB while fully mounted in the circuit without boot lockups.
2. **Through-Hole Capacitor Socket (`C2`):**
   * Standard 5.08 mm (200 mil) pitch through-hole footprint (`P=5.08 mm`, 1.0 mm drill).
   * Allows manual installation or socketing of standard film (polypropylene / CBB) or high-voltage NP0/C0G ceramic capacitors to customize resonant frequency or match non-standard coils.
3. **Screw Terminal Block (`J1`):**
   * Standard 2-pin screw terminal block (`KF301-2P`, 5.08 mm pitch, 1.3 mm drill).
   * Located at the top-right edge, **well clear of the tall 16×18 mm inductor (`L1`)**, with horizontal wire entry facing the board edge for effortless screwdriver access.
   * Allows securely clamping external ferrite bar antennas or loop antennas.
4. **Bedside Manual Sync Pushbutton (`SW1` & `J3`):**
   * Onboard 6×6 mm tactile pushbutton (`SW1`) + 2-pin external header (`J3`) wired to **GPIO 3** with a **10 kΩ pull-up (`R6`)**.
   * One-touch instant manual time broadcast without needing a smartphone or web browser. Pressing during broadcast aborts the transmission immediately. Also configured as a low-power deep-sleep wakeup source.
5. **I2C Expansion Header (`J2`):**
   * Standard 4-pin 2.54 mm header (`GND`, `+3V3`, `SCL/GPIO5`, `SDA/GPIO4`) with dedicated **4.7 kΩ pull-ups (`R4`, `R5`)**.
   * Pinout directly matches popular 0.96" SSD1306 / SH1106 I2C OLED displays and environmental sensors (BME280, SHT31).
6. **Clean SMT Bill of Materials ($0 Setup Cost):**
   * Pre-assembled by JLCPCB with **11 SMD components** (8 unique line items).
   * Every single SMD component, including the **tactile sync button (`SW1`)**, is a verified **JLCPCB Basic Component** ($0.00 feeder loading fee).
7. **Zero Bedside Light Pollution:**
   * No LEDs are placed on the carrier board to prevent unwanted illumination in a dark bedroom.
   * The ESP32-C3 SuperMini's onboard LED (GPIO 8) provides a subtle, calm breathing pulse only while a broadcast is actively running, remaining 100% dark during standby.

---

## Directory Contents

```
pcb/smd/
├── MultiBand6_Beacon.kicad_pro     # KiCad 10 / 9 Project file
├── MultiBand6_Beacon.kicad_sch     # KiCad Schematic file
├── MultiBand6_Beacon.kicad_pcb     # KiCad 2-Layer PCB Layout file (58x36 mm)
├── MultiBand6_Beacon_Gerbers.zip   # Ready-to-order Gerbers + Drill archive for JLCPCB
├── MultiBand6_Beacon-drc.rpt       # Clean KiCad DRC Report (0 errors, 0 warnings, 0 unconnected)
├── make_pcb.py                     # Automated Python layout & manufacturing generator
├── MultiBand6_Beacon_Gerbers/      # Raw JLCPCB-formatted Gerbers & Drills
│   ├── MultiBand6_Beacon-F_Cu.gtl
│   ├── MultiBand6_Beacon-B_Cu.gbl
│   ├── MultiBand6_Beacon-F_Mask.gts
│   ├── MultiBand6_Beacon-B_Mask.gbs
│   ├── MultiBand6_Beacon-F_Silkscreen.gto
│   ├── MultiBand6_Beacon-B_Silkscreen.gbo
│   ├── MultiBand6_Beacon-F_Paste.gtp
│   ├── MultiBand6_Beacon-B_Paste.gbp
│   ├── MultiBand6_Beacon-Edge_Cuts.gm1
│   ├── MultiBand6_Beacon-PTH.drl   # Plated Through-Hole Drill file
│   ├── MultiBand6_Beacon-NPTH.drl  # Non-Plated Through-Hole Drill file
│   └── MultiBand6_Beacon-job.gbrjob
├── bom.csv                         # SMT Bill of Materials (with LCSC Basic Part #s)
└── positions.csv                   # Centroid Pick-and-Place (CPL) file (calibrated coordinates & rotations)
```

> [!NOTE]
> **Looking for a 100% hand-solderable through-hole DIY design?** Check out [`pcb/hole-through/`](../hole-through/), which features an enlarged $70\text{ mm} \times 46\text{ mm}$ layout accommodating standard axial resistors, DO-41 diode, TO-92 transistor, and M3 mounting holes with zero surface mount components.

---

## Bill of Materials (SMT Assembly via JLCPCB)

All 11 SMD parts below are **JLCPCB Basic Components** ($0.00 part-loading fee):

| Designator | Value | Package | Description | LCSC Part # | JLCPCB Type |
| :--- | :--- | :--- | :--- | :--- | :--- |
| **SW1** | TS-1187A-B-A-B | SMD 5.1×5.1mm | Momentary Manual Sync Tactile Switch (GPIO 3) | `C318884` | **Basic** |
| **Q1** | MMBT2222A | SOT-23 | 600mA 40V NPN RF Switch Transistor | `C8512` | **Basic** |
| **D1** | 1N5819HW (B5819W) | SOD-123 | 1A 40V Schottky Inductive Clamp Diode | `C8598` | **Basic** |
| **C1** | 1.5nF (1500pF) | 0805 | 50V X7R Ceramic LC Tank Resonator | `C1717` | **Basic** |
| **C3, C4** | 10µF | 0805 | 25V X5R Ceramic Power Supply Decoupling | `C15850` | **Basic** |
| **R1** | 1kΩ | 0805 | 1% 1/8W Base Drive Resistor | `C17513` | **Basic** |
| **R2** | 220Ω | 0805 | 1% 1/8W Tank Current Limiter / Q Damping | `C17560` | **Basic** |
| **R4, R5** | 4.7kΩ | 0805 | 1% 1/8W I2C Bus Pull-Ups (SDA/SCL) | `C17673` | **Basic** |
| **R6** | 10kΩ | 0805 | 1% 1/8W Pushbutton Pull-Up (GPIO 3) | `C17414` | **Basic** |

### Hand-Soldered Through-Hole Components

| Designator | Description | Recommended Part | Sourcing |
| :--- | :--- | :--- | :--- |
| **U1** | ESP32-C3 SuperMini Socket | 2× 1×8 Female Header 2.54 mm | Standard headers |
| **L1** | 16×18 mm 3.5 mH Drum Core Inductor | Open magnetic circuit radial inductor | AliExpress / Taobao / LCSC |
| **J1** | External Antenna Terminal Block | 2-pin 5.08 mm pitch screw terminal (KF301-2P) | Standard terminal block |
| **J2** | I2C Display Header | 1×4 Pin Header (Male or Female) 2.54 mm | Standard 2.54 mm header |
| **J3** | External Sync Button Header | 1×2 Pin Header 2.54 mm | Standard 2.54 mm header |
| **C2** | Auxiliary Tuning Capacitor Socket | Standard 5.08 mm pitch through-hole capacitor socket | Optional for tuning |

---

## How to Order from JLCPCB

1. **PCB Fabrication:**
   * Go to [JLCPCB.com](https://jlcpcb.com/) and click **Order Now**.
   * Upload `MultiBand6_Beacon_Gerbers.zip` (located in this folder).
   * Dimensions: **58 mm × 36 mm** (auto-detected).
   * Layers: **2 Layers**, Thickness: **1.6 mm**, Surface Finish: **HASL (with lead)** or **LeadFree HASL**.
2. **SMT Assembly:**
   * Turn ON **PCB Assembly** (Assemble Top Side).
   * Upload `bom.csv` as the **BOM**.
   * Upload `positions.csv` as the **CPL (Pick-and-Place)** file.
   * All 11 SMD parts are automatically assigned as **Basic Parts** ($0.00 setup fees).
   * Confirm the 3D preview alignment and place your order!

---

## 📜 Hardware License

Licensed under the **[CERN Open Hardware Licence Version 2 - Strongly Reciprocal (CERN-OHL-S v2)](../../LICENSES/CERN-OHL-S-v2.txt)** (`CERN-OHL-S-2.0`). **Commercial License Available** for proprietary/closed-source manufacturing — see [`LICENSE`](../../LICENSE).

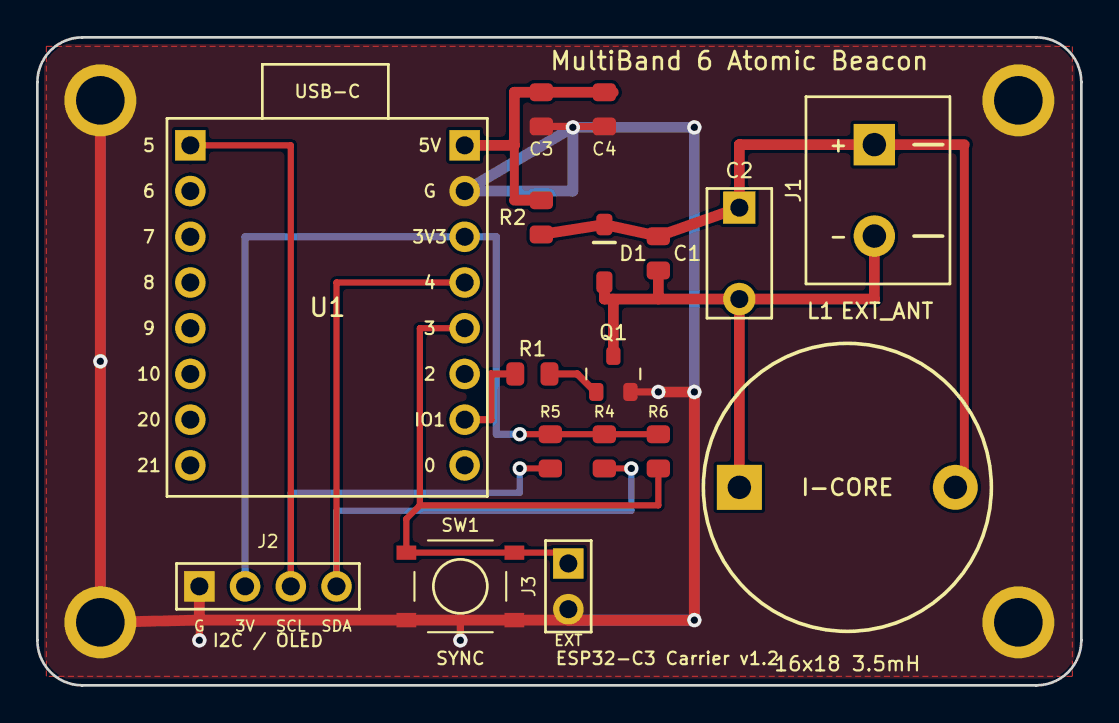
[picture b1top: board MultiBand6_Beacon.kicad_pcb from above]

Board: 2 copper layers, 58.0 x 36.0 mm, 17 parts (0 on the bottom side), 10 nets.

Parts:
C1: 1.5nF; C_0805_2012Metric
C2: THT-CAP; C_Rect_L7.2mm_W3.5mm_P5.08mm
C3: 10uF; C_0805_2012Metric
C4: 100nF; C_0805_2012Metric
D1: B5819W; D_SOD-123
J1: ANT_EXT; TerminalBlock_bornier-2_P5.08mm
J2: I2C_OLED; PinHeader_1x04_P2.54mm_Vertical
J3: EXT_SYNC; PinHeader_1x02_P2.54mm_Vertical
L1: 16x18 3.5mH; L_Radial_D16.0mm_P12.0mm_16x18_I-Type
Q1: MMBT2222A; SOT-23
R1: 1k; R_0805_2012Metric
R2: 220R; R_0805_2012Metric
R4, R5: 4.7k; R_0805_2012Metric
R6: 10k; R_0805_2012Metric
SW1: TS-1187A; SW_Push_1P1T_XKB_TS-1187A
U1: ESP32-C3-SuperMini; ESP32-C3-SuperMini_Socket

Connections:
+3V3: J2.2, R4.1, R5.1, R6.1, U1.11
+5V: C3.1, C4.1, R2.1, U1.9
GND: C3.2, C4.2, J2.1, J3.2, Q1.2, SW1.2, U1.10
GPIO1_CARRIER: R1.1, U1.15
GPIO3: J3.1, R6.2, SW1.1, U1.13
GPIO4: J2.4, R4.2, U1.12
GPIO5: J2.3, R5.2, U1.1
NET_BASE: Q1.1, R1.2
NET_TANK_HI: C1.1, C2.1, D1.1, J1.1, L1.2, R2.2
NET_TANK_SW: C1.2, C2.2, D1.2, J1.2, L1.1, Q1.3

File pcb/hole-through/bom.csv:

Designator,Value,Package / Footprint,Lead Spacing / Pitch,Description,Recommended Part / Type
U1,ESP32-C3 SuperMini,2x 1x8 Socket Header,P=2.54mm (600mil row spacing),RISC-V Wi-Fi/BLE MCU Module,Standard ESP32-C3 SuperMini
Q1,C1815 (or 2N2222),TO-92,P=2.54mm Inline,Small Signal NPN RF Switch Transistor,2SC1815 (E-C-B) or 2N2222 (E-B-C)
D1,1N5819,DO-41 Axial,P=10.16mm (400mil),1A 40V Schottky Inductive Clamp Diode,1N5819 (or 1N4148 / 1N4007)
R1,1k,Axial DIN0207,P=10.16mm (400mil),1/4W 5% Metal/Carbon Film Base Resistor,Standard 1k 1/4W Resistor
R2,220R,Axial DIN0207,P=10.16mm (400mil),1/4W 5% Metal/Carbon Film Damping Resistor,Standard 220R 1/4W Resistor
R4,4.7k,Axial DIN0207,P=10.16mm (400mil),1/4W 5% Metal Film I2C SDA Pull-Up,Standard 4.7k 1/4W Resistor
R5,4.7k,Axial DIN0207,P=10.16mm (400mil),1/4W 5% Metal Film I2C SCL Pull-Up,Standard 4.7k 1/4W Resistor
R6,10k,Axial DIN0207,P=10.16mm (400mil),1/4W 5% Metal Film Pushbutton Pull-Up,Standard 10k 1/4W Resistor
C1,1.5nF,Radial / Box Film,P=5.08mm (200mil),1.5nF (1500pF / code 152) 50V+ Tank Resonator,Metallized Film / C0G Ceramic
C2,Optional Socket,Box Film / Radial,P=5.08mm (200mil),Auxiliary Tank Tuning Capacitor Socket,Film / Ceramic Capacitor
C3,10uF,Radial Electrolytic (D=5mm),P=2.54mm (100mil),10uF 25V+ Bulk Decoupling Capacitor,Miniature Radial Electrolytic
C4,100nF,Radial Ceramic Disc / MLCC,P=5.08mm (200mil),100nF (0.1uF / code 104) 50V RF Bypass,Ceramic Disc / Multilayer Ceramic
L1,3.5mH 16x18,Radial Drum Inductor,P=12.0mm (D=16mm),16x18mm 3.5mH I-Type Open Core Radiator,Standard 1618 3.5mH Inductor
J1,KF301-2P,Screw Terminal Block,P=5.08mm,2-Pin Screw Terminal for External Antenna,Generic KF301-2P 5.08mm
SW1,6x6mm Switch,Tactile Pushbutton,6.5mm x 4.5mm pin spacing,Bedside Manual Sync Momentary Pushbutton,Standard 6x6x5mm Tactile Switch
J2,1x4 Header,Pin Header Male/Female,P=2.54mm,I2C Display Expansion Header (GND/3V3/SCL/SDA),Standard 2.54mm Header
J3,1x2 Header,Pin Header Male,P=2.54mm,External Pushbutton Header (Parallel with SW1),Standard 2.54mm Header
H1-H4,M3 Holes,Mounting Hole,D=3.2mm (6mm pad),Corner M3 Chassis / Standoff Mounting,Standard M3 Screws / Standoffs

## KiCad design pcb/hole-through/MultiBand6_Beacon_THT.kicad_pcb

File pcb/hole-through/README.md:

# MultiBand 6 ESP32 Atomic Beacon — Through-Hole (THT) Edition

A 100% through-hole, hand-solderable DIY carrier board for the MultiBand 6 ESP32 Atomic Clock Beacon transmitter. Designed specifically for easy assembly with standard hobbyist soldering equipment—**zero SMD components required**.

---

## 📐 Board Specifications

| Parameter | Value |
| :--- | :--- |
| **Dimensions** | $70.0\text{ mm} \times 46.0\text{ mm}$ ($2.76" \times 1.81"$) |
| **Layers** | 2-layer FR-4 ($1.6\text{ mm}$ standard thickness, $1\text{ oz}$ copper) |
| **Auxiliary Origin** | Bottom-left corner $(0.0, 46.0)$ canvas $\to$ $(0, 0)$ manufacturing origin |
| **Mounting** | $4\times \text{M3}$ mounting holes ($3.2\text{ mm}$ drill, $6.0\text{ mm}$ annular ring) |
| **Clearances** | $\ge 0.2\text{ mm}$ trace clearance, wide $0.6\text{ mm}$ RF tank buses |
| **Ground Plane** | Continuous solid ground pour on bottom layer (`B.Cu`) with thermal reliefs |
| **DRC Status** | **0 Errors, 0 Warnings, 0 Unconnected Pads** |

---

## 🛠️ Complete Bill of Materials (BOM)

All components use standard through-hole footprints available on DigiKey, Mouser, LCSC, AliExpress, or eBay:

| Ref | Value / Part | Footprint & Lead Pitch | Description & Sourcing Notes |
| :--- | :--- | :--- | :--- |
| **$U_1$** | ESP32-C3 SuperMini | $2\times 1\times 8$ Female Socket Header ($2.54\text{ mm}$ pitch, $15.24\text{ mm}$ / $600\text{ mil}$ row spacing) | RISC-V Wi-Fi / BLE microcontroller module. Socket allows easy removal or flashing. |
| **$Q_1$** | 2SC1815 (or 2N2222) | TO-92 Inline ($2.54\text{ mm}$ lead spacing) | NPN RF switching transistor. Silkscreen marked with explicit **E, C, B** labels. *(See Transistor Pinout Note below)* |
| **$D_1$** | 1N5819 (or 1N4148 / 1N4007) | DO-41 Axial ($10.16\text{ mm}$ / $400\text{ mil}$ pitch) | 1A 40V Schottky flyback clamp diode across the tank inductor. |
| **$R_1$** | $1\text{ k}\Omega$ | Axial DIN0207 ($10.16\text{ mm}$ pitch, 1/4W) | ESP32 GPIO1 base drive resistor ($5\%$ or $1\%$ carbon/metal film). Boot-safe non-strapping pin. |
| **$R_2$** | $220\,\Omega$ | Axial DIN0207 ($10.16\text{ mm}$ pitch, 1/4W) | Tank supply current limiter / Q-damping resistor. |
| **$R_4$** | $4.7\text{ k}\Omega$ | Axial DIN0207 ($10.16\text{ mm}$ pitch, 1/4W) | $I^2C$ SDA line pull-up resistor. |
| **$R_5$** | $4.7\text{ k}\Omega$ | Axial DIN0207 ($10.16\text{ mm}$ pitch, 1/4W) | $I^2C$ SCL line pull-up resistor. |
| **$R_6$** | $10\text{ k}\Omega$ | Axial DIN0207 ($10.16\text{ mm}$ pitch, 1/4W) | Manual sync pushbutton pull-up resistor (to $+3.3\text{V}$). |
| **$C_1$** | $1.5\text{ nF}$ ($1500\text{ pF}$, code `152`) | Radial / Box Film ($5.08\text{ mm}$ / $200\text{ mil}$ pitch) | Main LC resonant tank capacitor ($50\text{V}+$ rated, metallized polypropylene or C0G/NP0 ceramic). |
| **$C_2$** | Tuning Capacitor Socket | Box Film / Radial ($5.08\text{ mm}$ / $200\text{ mil}$ pitch) | Auxiliary parallel capacitor socket for frequency fine-tuning (e.g. $100\text{ pF}$–$470\text{ pF}$ for JJY/WWVB/MSF). |
| **$C_3$** | $10\,\mu\text{F}$ | Radial Electrolytic ($D=5\text{ mm}$, $2.54\text{ mm}$ pitch) | $+5\text{V}$ bulk filter capacitor ($25\text{V}+$ rated). |
| **$C_4$** | $100\text{ nF}$ ($0.1\,\mu\text{F}$, code `104`) | Radial Disc / MLCC ($5.08\text{ mm}$ pitch) | High-frequency ceramic decoupling bypass capacitor ($50\text{V}$ rated). |
| **$L_1$** | $3.5\text{ mH}$ $16\times 18$ | Radial Drum / I-Core ($12.0\text{ mm}$ lead pitch, $D=16\text{ mm}$) | High-Q open-core ferrite inductor serving as the magnetic near-field transmitting antenna. |
| **$J_1$** | KF301-2P | $2$-Pin Screw Terminal ($5.08\text{ mm}$ pitch) | External antenna / loop coil connection block (`+` Tank Hi, `-` Switched Collector). |
| **$SW_1$** | $6\times 6\text{ mm}$ Tactile | $4$-pin THT Pushbutton ($6.5\text{ mm} \times 4.5\text{ mm}$ pin spacing) | Bedside momentary manual sync trigger button. |
| **$J_2$** | $1\times 4$ Pin Header | Male or Female ($2.54\text{ mm}$ pitch) | $I^2C$ OLED Display interface (`GND`, `3V3`, `SCL`, `SDA`). |
| **$J_3$** | $1\times 2$ Pin Header | Male ($2.54\text{ mm}$ pitch) | Remote sync button connection (wired in parallel with $SW_1$). |
| **$H_1$–$H_4$** | M3 Hardware | $3.2\text{ mm}$ drill | $4\times$ corner mounting holes for standard $M3$ standoffs or 3D-printed enclosure. |

---

## ⚡ Transistor Pinout Note ($Q_1$)

The board silkscreen features clear visual pin markings for the TO-92 transistor:
- **Default Footprint:** Asian standard **E-C-B** pinout (e.g., **2SC1815**, **2SC945**, **KSC1815**):
  - Top Pin = **Collector** (`C`) $\to$ Tank Switched Node
  - Middle Pin = **Base** (`B`) $\to$ Base Resistor $R_1$
  - Bottom Pin = **Emitter** (`E`) $\to$ Ground
- **Alternative US Pinout (2N2222 / 2N3904):**
  - Standard American TO-92 pinout is **E-B-C**. If using a 2N2222 or 2N3904, cross the Base and Collector leads or gently splay them to match the labeled holes: Pin 1 (`E`) to Ground, Pin 2 (`C`) to Collector, Pin 3 (`B`) to Base.

---

## 🔌 Headers & Connectors Pinout

### $I^2C$ Display Header ($J_2$)
Matches standard $0.96"$ or $1.3"$ SSD1306 / SH1106 $I^2C$ OLED pinout:
1. **GND** (Square Pad 1)
2. **3V3** (Pad 2)
3. **SCL** (Pad 3 $\to$ ESP32 GPIO5)
4. **SDA** (Pad 4 $\to$ ESP32 GPIO4)

### External Antenna Terminal ($J_1$)
For connecting an external ferrite rod antenna or resonant loop coil:
- **`+` (Pin 1):** Tank Supply Rail (`NET_TANK_HI`, $+5\text{V}$ through $R_2$)
- **`-` (Pin 2):** Switched Collector Rail (`NET_TANK_SW`, $Q_1$ Collector)

---

## 📦 Manufacturing with JLCPCB

The manufacturing package is pre-compiled and fully validated:

- **Gerber & Drill ZIP:** [`MultiBand6_Beacon_THT_Gerbers.zip`](file:///Users/robertlongbottom/dev/MultiBand6-ESP32-AtomicBeacon/pcb/hole-through/MultiBand6_Beacon_THT_Gerbers.zip)
- **Ordering Parameters:**
  - **Base Material:** FR-4
  - **Layers:** 2 Layers
  - **Dimensions:** $70\text{ mm} \times 46\text{ mm}$
  - **PCB Thickness:** $1.6\text{ mm}$
  - **PCB Color:** Green, Blue, Black, Purple, etc. (any standard color)
  - **Surface Finish:** HASL with lead or Lead-free HASL
  - **Copper Weight:** $1\text{ oz}$ ($35\,\mu\text{m}$)
  - **SMT Assembly:** **None / No** (all components are hand-soldered through-hole parts)

---

## 🪛 Recommended Soldering Order

For the cleanest and easiest hand-soldering assembly, solder components in order of physical height:

1. **Lowest Profile:** Resistors $R_1, R_2, R_4, R_5, R_6$ and Diode $D_1$ (bend leads $90^\circ$ and lay flat against the PCB). *Ensure $D_1$ cathode band aligns with the double-line silkscreen mark towards $+5\text{V}$*.
2. **Capacitors & Headers:** Ceramic capacitor $C_4$, film capacitors $C_1, C_2$, pin headers $J_2, J_3$, and the $2\times 1\times 8$ female socket for $U_1$.
3. **Transistor & Button:** $Q_1$ TO-92 transistor (observe `E-C-B` markings) and tactile pushbutton $SW_1$.
4. **Tall Components:** Electrolytic capacitor $C_3$ (observe `+`/`-` polarity), screw terminal block $J_1$, and the $16\times 18\text{ mm}$ power inductor $L_1$.
5. **Final Step:** Insert the ESP32-C3 SuperMini module into the socket headers with the USB-C port facing the board edge.

---

## 📜 Hardware License

Licensed under the **[CERN Open Hardware Licence Version 2 - Strongly Reciprocal (CERN-OHL-S v2)](../../LICENSES/CERN-OHL-S-v2.txt)** (`CERN-OHL-S-2.0`). **Commercial License Available** for proprietary/closed-source manufacturing — see [`LICENSE`](../../LICENSE).

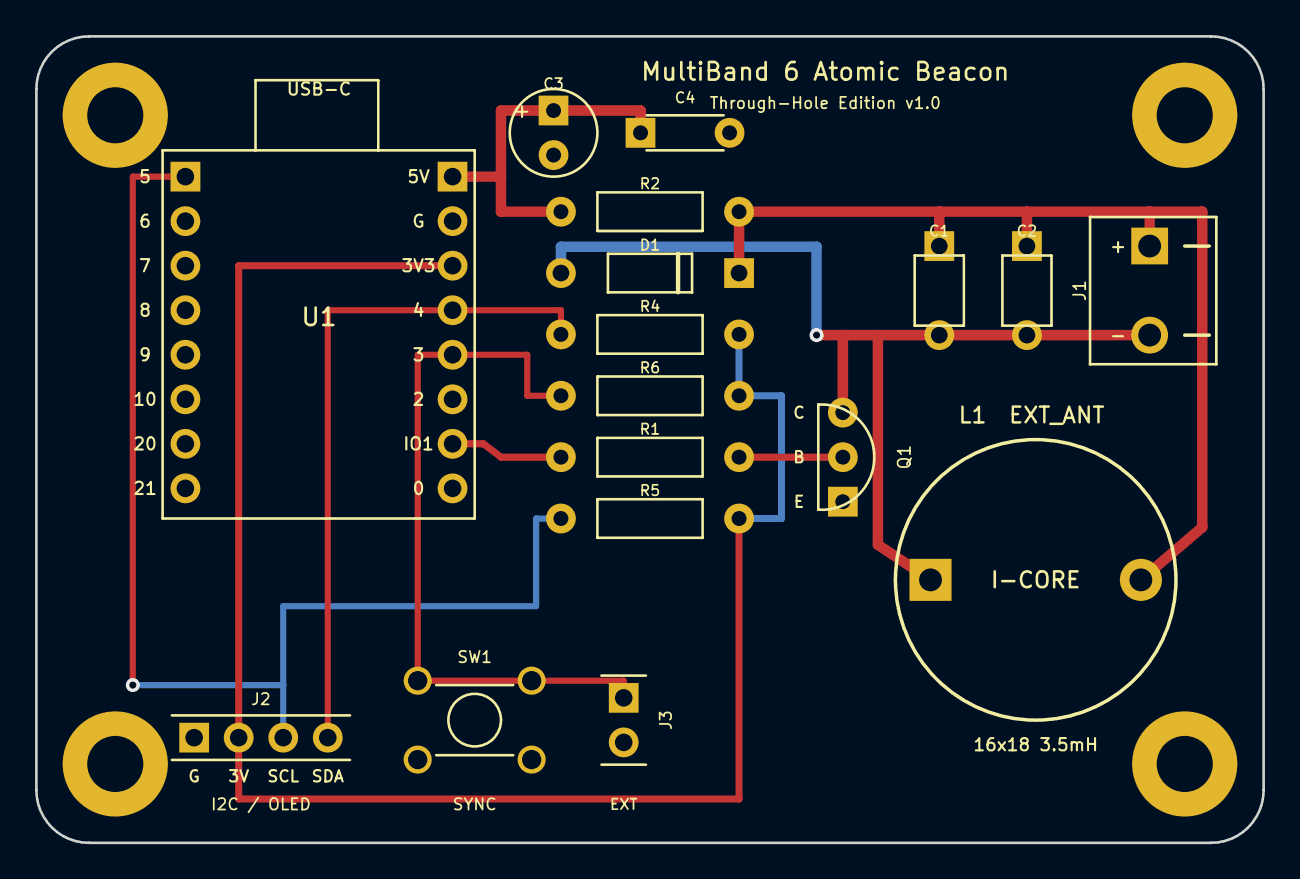
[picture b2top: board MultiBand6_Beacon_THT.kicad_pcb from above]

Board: 2 copper layers, 70.0 x 46.0 mm, 17 parts (0 on the bottom side), 10 nets.

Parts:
C1: 1.5nF; C_Rect_L7.2mm_W3.5mm_P5.08mm
C2: THT-CAP; C_Rect_L7.2mm_W3.5mm_P5.08mm
C3: 10uF; CP_Radial_D5.0mm_P2.50mm
C4: 100nF; C_Disc_D5.0mm_W2.5mm_P5.00mm
D1: 1N5819; D_DO-41_SOD81_P10.16mm_Horizontal
J1: ANT_EXT; TerminalBlock_bornier-2_P5.08mm
J2: I2C_OLED; PinHeader_1x04_P2.54mm_Vertical
J3: EXT_SYNC; PinHeader_1x02_P2.54mm_Vertical
L1: 16x18 3.5mH; L_Radial_D16.0mm_P12.0mm_16x18_I-Type
Q1: C1815; TO-92_Inline_Wide
R1: 1k; R_Axial_DIN0207_L6.3mm_D2.5mm_P10.16mm_Horizontal
R2: 220R; R_Axial_DIN0207_L6.3mm_D2.5mm_P10.16mm_Horizontal
R4, R5: 4.7k; R_Axial_DIN0207_L6.3mm_D2.5mm_P10.16mm_Horizontal
R6: 10k; R_Axial_DIN0207_L6.3mm_D2.5mm_P10.16mm_Horizontal
SW1: SYNC_BTN; SW_PUSH_6mm
U1: ESP32-C3-SuperMini; ESP32-C3-SuperMini_Socket

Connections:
+3V3: J2.2, R4.2, R5.2, R6.2, U1.11
+5V: C3.1, C4.1, R2.1, U1.9
GND: C3.2, C4.2, J2.1, J3.2, Q1.1, SW1.3, SW1.4, U1.10
GPIO1_CARRIER: R1.1, U1.15
GPIO3: J3.1, R6.1, SW1.1, SW1.2, U1.13
GPIO4: J2.4, R4.1, U1.12
GPIO5: J2.3, R5.1, U1.1
NET_BASE: Q1.3, R1.2
NET_TANK_HI: C1.1, C2.1, D1.1, J1.1, L1.2, R2.2
NET_TANK_SW: C1.2, C2.2, D1.2, J1.2, L1.1, Q1.2

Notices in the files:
README.md:
12. License & Commercial Use:
This project uses a dual reciprocal copyleft licensing structure so makers and builders stay free to build, modify, and share, while protecting the designs against closed-source commercial appropriation:
Firmware, Web UI & Tooling (`firmware-rust/`, `data/`, `docs/`):** Licensed under the **[GNU General Public License v3.0 (GPLv3)](LICENSES/GPL-3.0.txt)** (`GPL-3.0-only`).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
